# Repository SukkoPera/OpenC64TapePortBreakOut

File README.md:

# OpenC64TapePortBreakOut
OpenC64TapePortBreakOut is an Open Hardware PCB that breaks out all the pins on a Commodore 1530 Datassette Connector. It is mainly useful for building Tapuino devices.

### Example Uses
#### Commodore 1530 Datassetta Adapter for Commodore 16/Plus 4 Computers
OpenC64TapePortBreakOut can be used to make an ad adapter to connect a Commodore 1530 Datassette to a Commodore 16, Plus 4 and other members of the 264 family which use a 1531 Datasssette.

To do so, get a 7-pin Mini-Din cable-mount connector and solder each pin to the corresponding OpenC64TapePortBreakOut pin, using the following pinout:

|Pin#|Function|
|----|--------|
|1|GND        |
|2|Vcc        |
|3|Motor      |
|4|Read       |
|5|Write      |
|6|Sense      |
|7|NC (or GND)|

### License
OpenC64TapePortBreakOut is Open Hardware. If you make any modifications to the board, please contribute them back.

### Support the Project
Since the project is open you are free to get the PCBs made by your preferred manufacturer, however in case you want to support the development, you can order them from PCBWay through this link:

You get cheap, professionally-made and good quality PCBs, I get some credit that will help with this and [other projects](https://www.pcbway.com/project/member/shareproject/?bmbid=41100). You won't even have to worry about the various PCB options, it's all pre-configured for you!

Also, if you still have to register to that site, [you can use this link](https://www.pcbway.com/setinvite.aspx?inviteid=41100) to get some bonus initial credit (and yield me some more).

Again, if you want to use another manufacturer, feel free to, don't feel obligated :).

### Get Support
If you need help or have questions, you can join [the official Telegram group](https://t.me/joinchat/HUHdWBC9J9JnYIrvTYfZmg).

### Thanks
Thanks to Terje Abbedissen for supporting the development.

The following links were also useful:
- https://github.com/hackup/SD2IECplug

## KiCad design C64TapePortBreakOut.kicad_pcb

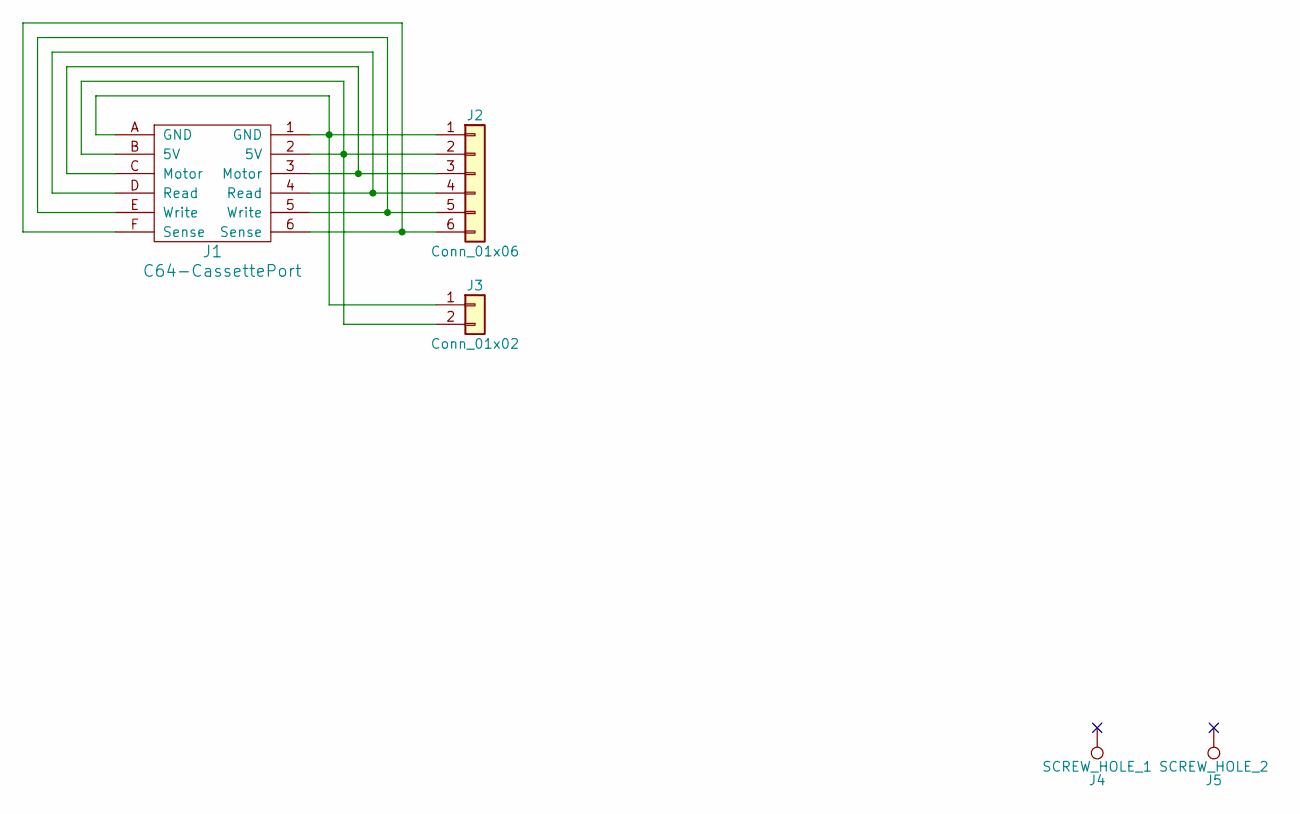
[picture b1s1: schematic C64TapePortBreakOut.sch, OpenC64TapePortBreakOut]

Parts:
J1: C64-CassettePort; C64-Cassette-Port-Male
J2: Conn_01x06; pin_strip_6
J3: Conn_01x02; pin_strip_2
J4: SCREW_HOLE_1; MountingHole_3mm_Pad
J5: SCREW_HOLE_2; MountingHole_3mm_Pad

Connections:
unnamed: J1.1 (GND), J1.A (GND), J2.1, J3.1
unnamed: J1.2 (5V), J1.B (5V), J2.2, J3.2
unnamed: J1.3 (Motor), J1.C (Motor), J2.3
unnamed: J1.4 (Read), J1.D (Read), J2.4
unnamed: J1.5 (Write), J1.E (Write), J2.5
unnamed: J1.6 (Sense), J1.F (Sense), J2.6

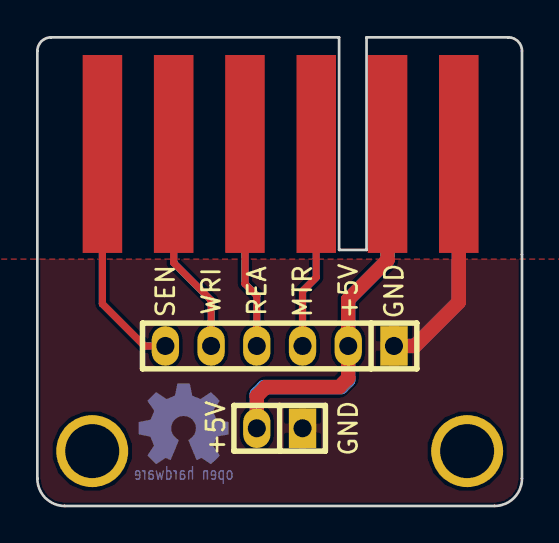
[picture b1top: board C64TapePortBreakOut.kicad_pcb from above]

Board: 2 copper layers, 26.9 x 26.0 mm, 5 parts (0 on the bottom side), 6 nets.

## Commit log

2018-01-08 Initial commit, ready for V1
2018-02-18 Remove ground plane and solder mask from edge connector
